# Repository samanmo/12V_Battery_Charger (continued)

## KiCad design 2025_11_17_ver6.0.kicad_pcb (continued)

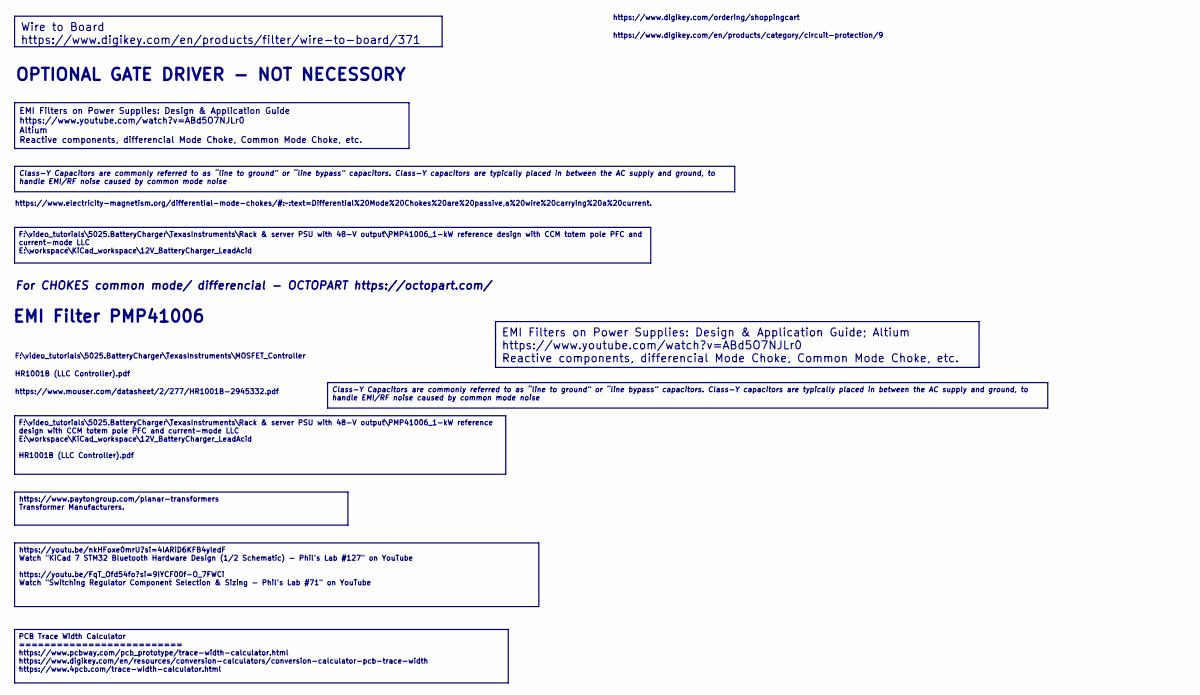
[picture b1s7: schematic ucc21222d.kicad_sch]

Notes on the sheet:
EMI Filter PMP41006
F:\video_tutorials\5025.BatteryCharger\TexasInstruments\MOSFET_Controller
https://www.digikey.com/en/products/category/circuit-protection/9
https://www.mouser.com/datasheet/2/277/HR1001B-2945332.pdf
For CHOKES common mode/ differencial - OCTOPART https://octopart.com/
https://www.digikey.com/ordering/shoppingcart
HR1001B (LLC Controller).pdf
OPTIONAL GATE DRIVER - NOT NECESSORY
https://www.electricity-magnetism.org/differential-mode-chokes/#:~:text=Differential%20Mode%20Chokes%20are%20passive,a%20wire%20carrying%20a%20current.
Wire to Board https://www.digikey.com/en/products/filter/wire-to-board/371
EMI Filters on Power Supplies: Design & Application Guide; Altium https://www.youtube.com/watch?v=ABd5O7NJLr0 Reactive components, differencial Mode Choke, Common Mode Choke, etc.
F:\video_tutorials\5025.BatteryCharger\TexasInstruments\Rack & server PSU with 48-V output\PMP41006_1-kW reference design with CCM totem pole PFC and current-mode LLC E:\workspace\KiCad_workspace\12V_BatteryCharger_LeadAcid HR1001B (LLC Controller).pdf
PCB Trace Width Calculator ========================== https://www.pcbway.com/pcb_prototype/trace-width-calculator.html https://www.digikey.com/en/resources/conversion-calculators/conversion-calculator-pcb-trace-width https://www.4pcb.com/trace-width-calculator.html
https://www.paytongroup.com/planar-transformers Transformer Manufacturers.
Class-Y Capacitors are commonly referred to as “line to ground” or “line bypass” capacitors. Class-Y capacitors are typically placed in between the AC supply and ground, to handle EMI/RF noise caused by common mode noise
F:\video_tutorials\5025.BatteryCharger\TexasInstruments\Rack & server PSU with 48-V output\PMP41006_1-kW reference design with CCM totem pole PFC and current-mode LLC E:\workspace\KiCad_workspace\12V_BatteryCharger_LeadAcid
https://youtu.be/nkHFoxe0mrU?si=4lARiD6KFB4yIedF Watch "KiCad 7 STM32 Bluetooth Hardware Design (1/2 Schematic) - Phil's Lab #127" on YouTube https://youtu.be/FqT_Ofd54fo?si=9IYCF00f-O_7FWCi Watch "Switching Regulator Component Selection & Sizing - Phil's Lab #71" on YouTube
EMI Filters on Power Supplies: Design & Application Guide https://www.youtube.com/watch?v=ABd5O7NJLr0 Altium Reactive components, differencial Mode Choke, Common Mode Choke, etc.

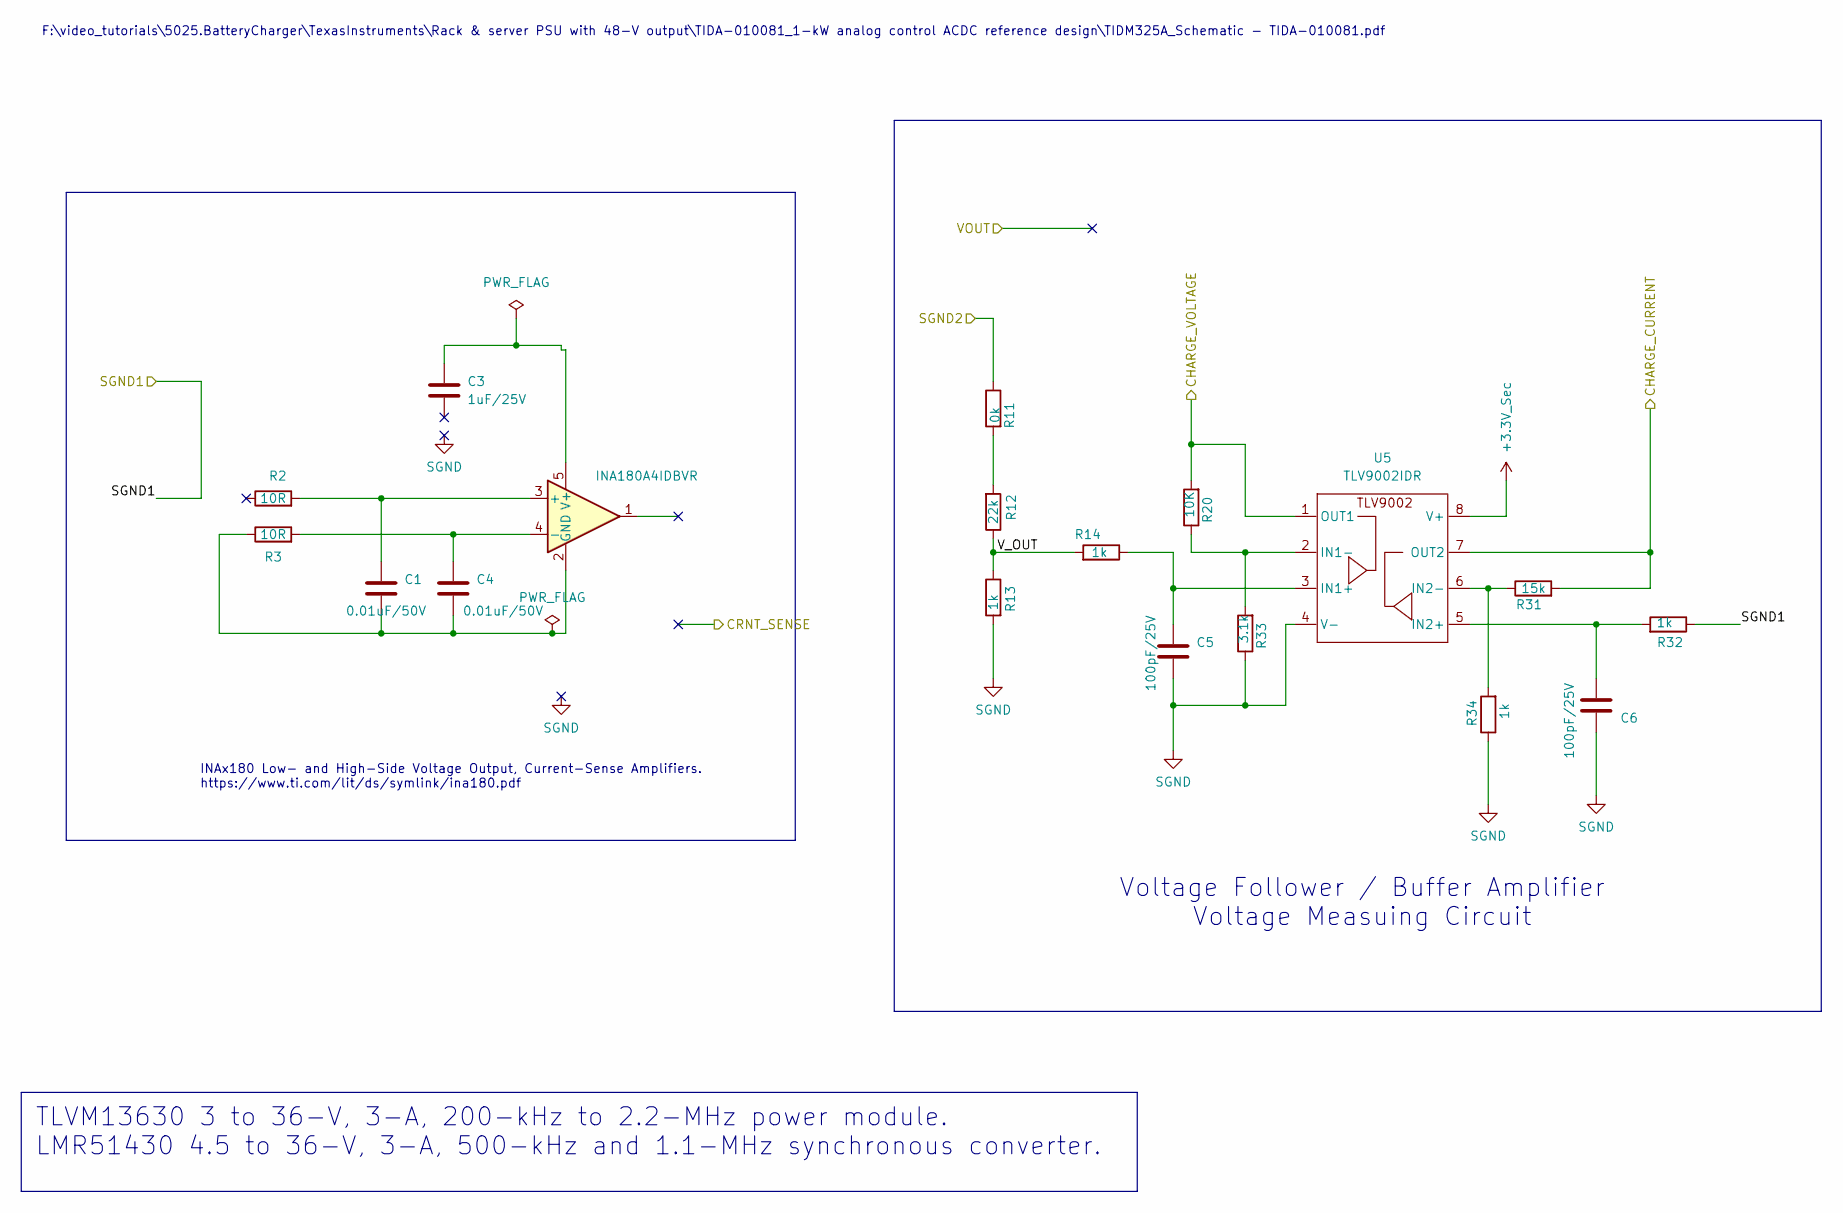
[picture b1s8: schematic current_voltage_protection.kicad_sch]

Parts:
C1, C4: 0.01uF/50V; C_0603_1608Metric_Pad1.08x0.95mm_HandSolder; Manufacturer_Part_Number GCM188R72A103KA37D; Digi-Key_PN 490-4781-1-ND
C3: 1uF/25V; C_0805_2012Metric_Pad1.18x1.45mm_HandSolder; Manufacturer_Part_Number CL21B105KBFNNNE; Digi-Key_PN 1276-1029-1-ND
C5, C6: 100pF/25V; C_0805_2012Metric_Pad1.18x1.45mm_HandSolder; Manufacturer_Part_Number CC0805KRX7R8BB103; Digi-Key_PN 311-3579-1-ND
R2, R3: 10R; R_1206_3216Metric_Pad1.30x1.75mm_HandSolder; Manufacturer_Part_Number RT1206DRE0710RL; Digi-Key_PN 311-2958-1-ND
R11: 0k; R_0805_2012Metric_Pad1.20x1.40mm_HandSolder; Manufacturer_Part_Number RC0805FR-076K8L; Digi-Key_PN 311-6.80KCRCT-ND
R12: 22k; R_0805_2012Metric_Pad1.20x1.40mm_HandSolder; Manufacturer_Part_Number RC0805FR-071KL; Digi-Key_PN 311-1.00KCRCT-ND
R13: 1k; R_0805_2012Metric_Pad1.20x1.40mm_HandSolder; Manufacturer_Part_Number RC0805FR-072K2L; Digi-Key_PN 311-2.20KCRCT-ND
R14, R32: 1k; R_0805_2012Metric_Pad1.20x1.40mm_HandSolder; Manufacturer_Part_Number RC0805FR-071KL; Digi-Key_PN 311-1.00KCRCT-ND
R20: 10K; R_0805_2012Metric_Pad1.20x1.40mm_HandSolder; Manufacturer_Part_Number RC0805JR-070RL; Digi-Key_PN 311-0.0ARCT-ND
R31: 15k; R_0805_2012Metric_Pad1.20x1.40mm_HandSolder; Manufacturer_Part_Number RC0805JR-070RL; Digi-Key_PN 311-0.0ARCT-ND
R33: 3.1k; R_0805_2012Metric_Pad1.20x1.40mm_HandSolder; Manufacturer_Part_Number RC0805JR-070RL; Digi-Key_PN 311-0.0ARCT-ND
R34: 1k; R_0805_2012Metric_Pad1.20x1.40mm_HandSolder; Manufacturer_Part_Number RC0805JR-070RL; Digi-Key_PN 311-0.0ARCT-ND
U4: INA180A4IDBVR; SOT-23-5; Manufacturer_Part_Number INA180A4IDBVR; Digi-Key_PN 296-47655-1-ND
U5: TLV9002IDR; D0008A_M; Manufacturer_Part_Number TLV9002IDR; Digi-Key_PN 296-47596-1-ND

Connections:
+3.3V_Sec: U5.8 (V+); also elsewhere on the board
/Output_Filtering/CHARGE_CURRENT_STM32: R31.2, U5.7 (OUT2); also elsewhere on the board
/Output_Filtering/CHARGE_VOLTAGE_STM32: R20.2, U5.1 (OUT1); also elsewhere on the board
/Output_Filtering/Current_voltage_protection/V_OUT: R12.1, R13.1, R14.2
/Output_Filtering/SGND1: R32.1; also elsewhere on the board
/Output_Filtering/SGND2: R11.1; also elsewhere on the board
unnamed: R11.2, R12.2
unnamed: C1.1, R2.2, U4.3 (+)
unnamed: C4.1, R3.2, U4.4 (-)
unnamed: C1.2, C4.2, R3.1, U4.2 (GND)
unnamed: C3.1, U4.5 (V+)
unnamed: C5.1, R14.1, U5.3 (IN1+)
unnamed: R20.1, R33.2, U5.2 (IN1-)
unnamed: C6.1, R32.2, U5.5 (IN2+)
unnamed: R31.1, R34.2, U5.6 (IN2-)
SGND: C5.2, C6.2, R13.2, R33.1, R34.1, U5.4 (V-); also elsewhere on the board

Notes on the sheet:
F:\video_tutorials\5025.BatteryCharger\TexasInstruments\Rack & server PSU with 48-V output\TIDA-010081_1-kW analog control ACDC reference design\TIDM325A_Schematic - TIDA-010081.pdf
INAx180 Low- and High-Side Voltage Output, Current-Sense Amplifiers. https://www.ti.com/lit/ds/symlink/ina180.pdf
Voltage Follower / Buffer Amplifier Voltage Measuing Circuit
TLVM13630 3 to 36-V, 3-A, 200-kHz to 2.2-MHz power module. LMR51430 4.5 to 36-V, 3-A, 500-kHz and 1.1-MHz synchronous converter.

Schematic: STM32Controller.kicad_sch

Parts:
C111, C115: 44uF/25V; C_1206_3216Metric_Pad1.33x1.80mm_HandSolder; Manufacturer_Part_Number C3216X5R1E476M160AC; Digi-Key_PN 445-8047-1-ND
C112, C114: 2.2uF/25V; C_0805_2012Metric_Pad1.18x1.45mm_HandSolder; Manufacturer_Part_Number CL21B225KAFNFNE; Digi-Key_PN 1276-2953-1-ND
C113: 0.1uF/25V; C_0805_2012Metric_Pad1.18x1.45mm_HandSolder; Manufacturer_Part_Number CC0805KRX7R9BB104; Digi-Key_PN 311-1140-1-ND
J4: Screw_Terminal_01x02 pwm; TerminalBlock_Phoenix_MKDS-1,5-2-5.08_1x02_P5.08mm_Horizont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
J6, J13, J14, J16: Conn_01x01_Pin; PinHeader_1x01_P2.54mm_Vertical
L12: 5.6uH/5A; L_Pulse_PA4341.562NLT_7.6x6.9mm; Manufacturer_Part_Number PA4341.562NLT; Digi-Key_PN 553-3417-1-ND
R53, R55, R56, R58, R59, R60, R62, R63: 0; R_0805_2012Metric_Pad1.20x1.40mm_HandSolder; not fitted
R150, R152: 100k; R_0805_2012Metric_Pad1.20x1.40mm_HandSolder; Manufacturer_Part_Number RC0805FR-07100KL; Digi-Key_PN 311-100KCRCT-ND
R151, R153: 22.6k; R_0805_2012Metric_Pad1.20x1.40mm_HandSolder; Manufacturer_Part_Number RC0805FR-0722K1L; Digi-Key_PN 311-22.1KCRCT-ND
R167: 0R; R_0805_2012Metric_Pad1.20x1.40mm_HandSolder; Manufacturer_Part_Number RC0805JR-070RL; Digi-Key_PN 311-0.0ARCT-ND
U6: LM317_TO-220; TO-220-3_Vertical
U10: WeAct_BluePill; WeAct_BluekPill_Correct_Size
U25: LMR51430XDDCR; SOT-23-THIN-6_DDC_TEX-M; Manufacturer_Part_Number LMR51430XDDCR; Digi-Key_PN 296-LMR51430XDDCRCT-ND

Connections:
+3.3V_Sec: J6.1, R63.1, R167.2; also elsewhere on the board
/LLC_Power/+20V: C112.1, J4.2, U25.3 (VIN), U25.5 (EN); also elsewhere on the board
/Output_Filtering/CHARGE_CURRENT_STM32: R59.1; also elsewhere on the board
/Output_Filtering/CHARGE_VOLTAGE_STM32: R56.1; also elsewhere on the board
/Output_Filtering/CRNT_SENSE_STM32: R58.1
/Output_Filtering/FBR2_STM32: R60.1; also elsewhere on the board
/Output_Filtering/FBR_STM32: R55.2; also elsewhere on the board
/Output_Filtering/STM32Controller/3V3_STM32: R63.2, U10.38 (3V3)
/Output_Filtering/STM32Controller/+3.3V_Sec_SW: C113.1, L12.2, U25.2 (SW)
/Output_Filtering/STM32Controller/+3.3V_Sec_SW1: C111.2, L12.1, R150.1, R167.1
/Output_Filtering/STM32Controller/FB_LMR51430_3V3: R150.2, R151.1, U25.4 (FB)
/Output_Filtering/STM32Controller/GND_STM32: R53.1, U10.19 (GND)
/Output_Filtering/STM32Controller/STM32_5V: R62.1
unnamed: C114.1, J13.1, U6.3 (VI)
unnamed: C115.2, J14.1, R152.1, U6.2 (VO)
unnamed: C114.2, C115.1, J16.1, R153.2
unnamed: R152.2, R153.1, U6.1 (ADJ)
unnamed: R62.2, U10.18 (5V)
unnamed: R59.2, U10.27 (PA1)
unnamed: R56.2, U10.28 (PA2)
unnamed: R58.2, U10.33 (PA7)
unnamed: R55.1, U10.5 (PA8)
unnamed: R60.2, U10.37 (PB10)
unnamed: C113.2, U25.6 (CB)
SGND: C111.1, C112.2, J4.1, R53.2, R151.2, U25.1 (GND); also elsewhere on the board

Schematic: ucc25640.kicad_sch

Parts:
C24, C30: 100pF; C_0805_2012Metric_Pad1.18x1.45mm_HandSolder
C25: 0.01uF/25V; C_0805_2012Metric_Pad1.18x1.45mm_HandSolder; Manufacturer_Part_Number CC0805KRX7R8BB103; Digi-Key_PN 311-3579-1-ND
C26, C27: 100pF/50V; C_0805_2012Metric_Pad1.18x1.45mm_HandSolder; Manufacturer_Part_Number CC0805JRNPO9BN101; Digi-Key_PN 311-1111-1-ND
C28: 2.2uF/25V; C_0805_2012Metric_Pad1.18x1.45mm_HandSolder; Manufacturer_Part_Number CL21B225KAFNFNE; Digi-Key_PN 1276-2953-1-ND
C29: 0.01uF; C_0805_2012Metric_Pad1.18x1.45mm_HandSolder
C31: 1nF/50V; C_0805_2012Metric_Pad1.18x1.45mm_HandSolder; Manufacturer_Part_Number CC0805JRNPO9BN101; Digi-Key_PN 311-1111-1-ND
C46: 2.2nF; C_0805_2012Metric_Pad1.18x1.45mm_HandSolder
C50: 4.7uF/25V; C_0805_2012Metric_Pad1.18x1.45mm_HandSolder; Manufacturer_Part_Number C2012X5R1E475K125AB; Digi-Key_PN 445-4116-1-ND
C51: 27nF/68nF/22nF/15V; C_0805_2012Metric_Pad1.18x1.45mm_HandSolder; Manufacturer_Part_Number C0805C273K5RAC7800; Digi-Key_PN 399-C0805C273K5RAC7800CT-ND
D39: 600V 1A SMA; SODFL3616X98N; Manufacturer_Part_Number SM4005PL-TP; Digi-Key_PN SM4005PL-TPMSCT-ND
D40: 100V 1A SMA; SODFL3616X98N; Manufacturer_Part_Number SM4005PL-TP; Digi-Key_PN SM4005PL-TPMSCT-ND
FB1: FerriteBead; L_0805_2012Metric_Pad1.05x1.20mm_HandSolder
IC3, IC4: UCC27517DBVR; SOT-23-5_HandSoldering; Mouser Part Number 595-UCC27517DBVR
R4, R5: 5.1M; R_0805_2012Metric_Pad1.20x1.40mm_HandSolder; Manufacturer_Part_Number RC0805FR-075M1L; Digi-Key_PN 13-RC0805FR-075M1LCT-ND
R6: 5.6M; R_0805_2012Metric_Pad1.20x1.40mm_HandSolder; Manufacturer_Part_Number RC0805FR-075M6L; Digi-Key_PN 13-RC0805FR-075M6LCT-ND
R7: 127k; R_0805_2012Metric_Pad1.20x1.40mm_HandSolder; Manufacturer_Part_Number RC0805FR-07127KL; Digi-Key_PN 311-127KCRCT-ND
R8, R9, R10, R24: 1.65K; R_0805_2012Metric_Pad1.20x1.40mm_HandSolder; Manufacturer_Part_Number RC0805FR-071K65L; Digi-Key_PN 311-1.65KCRCT-ND
R15, R17, R21: 0; R_0805_2012Metric_Pad1.20x1.40mm_HandSolder
R16: 2.00k; R_0805_2012Metric_Pad1.20x1.40mm_HandSolder
R18: 10k/8.2k; R_0805_2012Metric_Pad1.20x1.40mm_HandSolder
R19: 15k; R_0805_2012Metric_Pad1.20x1.40mm_HandSolder
R22: 30k; R_0805_2012Metric_Pad1.20x1.40mm_HandSolder
R23: 3.3k; R_0805_2012Metric_Pad1.20x1.40mm_HandSolder
R27: 100R; R_1206_3216Metric_Pad1.30x1.75mm_HandSolder; Manufacturer_Part_Number RC1206FR-07100RL; Digi-Key_PN 311-100FRCT-ND
R28: 10R; R_1206_3216Metric_Pad1.30x1.75mm_HandSolder; Manufacturer_Part_Number RC1206FR-07100RL; Digi-Key_PN 311-100FRCT-ND
R41: 2.2R; R_1206_3216Metric_Pad1.30x1.75mm_HandSolder; Manufacturer_Part_Number RC1206FR-072R2L; Digi-Key_PN 311-2.20FRCT-ND
R42: 549k; R_0805_2012Metric_Pad1.20x1.40mm_HandSolder; Manufacturer_Part_Number RC0805FR-07549KL; Digi-Key_PN 311-549KCRCT-ND
R43: 195k; R_0805_2012Metric_Pad1.20x1.40mm_HandSolder; Manufacturer_Part_Number RC0805FR-07140KL; Digi-Key_PN 311-140KCRCT-ND
R44, R45: 0R; R_0805_2012Metric_Pad1.20x1.40mm_HandSolder; Manufacturer_Part_Number RC0805JR-070RL; Digi-Key_PN 311-0.0ARCT-ND
R46, R47, R68: 0; R_0805_2012Metric_Pad1.20x1.40mm_HandSolder; Manufacturer_Part_Number RC0805FR-07549KL; Digi-Key_PN 311-549KCRCT-ND
R57: 1k; R_0805_2012Metric_Pad1.20x1.40mm_HandSolder
R69, R70: 8R; R_0805_2012Metric_Pad1.20x1.40mm_HandSolder
U1: VO618A; SMD-4-OPT7_VO618A_VIS-M
U2: UCC256404DDBR; DDB0014A-IPC_A
U3: TL431LP; TO-92_Inline_Wide

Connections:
/LLC_Power/BW: U2.8 (BW); also elsewhere on the board
/LLC_Power/ISNS: U2.6 (ISNS); also elsewhere on the board
/LLC_Power/LLC-HOA: R44.2; also elsewhere on the board
/LLC_Power/LLC-HSA: C28.2, IC3.2 (GND), IC3.4 (IN-), U2.16 (HS); also elsewhere on the board
/LLC_Power/LLC-LOA: R45.2; also elsewhere on the board
/LLC_Power/RVCC: C50.1, IC4.1 (VDD), R41.2, R46.1, U2.12 (RVCC)
/LLC_Power/UCC25640/BLK: C25.1, R6.2, R7.1, R27.1
/LLC_Power/UCC25640/BLK1: C26.1, R27.2, U2.4 (BLK)
/LLC_Power/UCC25640/FB: FB1.1, R28.1
/LLC_Power/UCC25640/FB1: C27.1, R28.2, U2.5 (FB)
/LLC_Power/UCC25640/HB: C28.1, D40.1 (K), IC3.1 (VDD), U2.14 (HB)
/LLC_Power/UCC25640/LL: C51.2, R42.2, R47.1, U2.9 (LL_SS)
/LLC_Power/UCC25640/VCCP1: R68.2, U2.3 (VCC)
/LLC_Power/VCCP: R68.1; also elsewhere on the board
/LLC_Power/VCR: U2.7 (VCR); also elsewhere on the board
/LLC_Power/V_BUS: R4.1, R10.1; also elsewhere on the board
/VOUT: R15.1; also elsewhere on the board
unnamed: C24.1, FB1.2, U1.4
unnamed: C29.2, R22.1
unnamed: C46.1, R57.2
unnamed: C46.2, R15.2, R17.2, R18.2
unnamed: D39.2 (A), R41.1
unnamed: D39.1 (K), D40.2 (A)
unnamed: IC3.3 (IN+), R69.2
unnamed: IC3.5 (OUT), R44.1
unnamed: IC4.3 (IN+), R70.2
unnamed: IC4.5 (OUT), R45.1
unnamed: R4.2, R5.1
unnamed: R5.2, R6.1
unnamed: R8.2, R9.1
unnamed: R8.1, R10.2
unnamed: R16.1, R18.1, R57.1, U1.1
unnamed: R17.1, R19.1
unnamed: R21.1, U1.3
unnamed: R9.2, R24.1
unnamed: R42.1, R46.2
unnamed: R43.1, R47.2
unnamed: R69.1, U2.15 (HO)
unnamed: R24.2, U2.1 (HV)
unnamed: R70.1, U2.10 (LO)
unnamed: C29.1, C30.1, R16.2, U1.2, U3.3 (K)
unnamed: C30.2, C31.1, R19.2, R22.2, R23.1, U3.1 (REF)
PGND1: C24.2, C25.2, C26.2, C27.2, C50.2, C51.1, IC4.2 (GND), IC4.4 (IN-), R7.2, R21.2, R43.2, U2.11 (GND); also elsewhere on the board
SGND: C31.2, R23.2, U3.2 (A); also elsewhere on the board

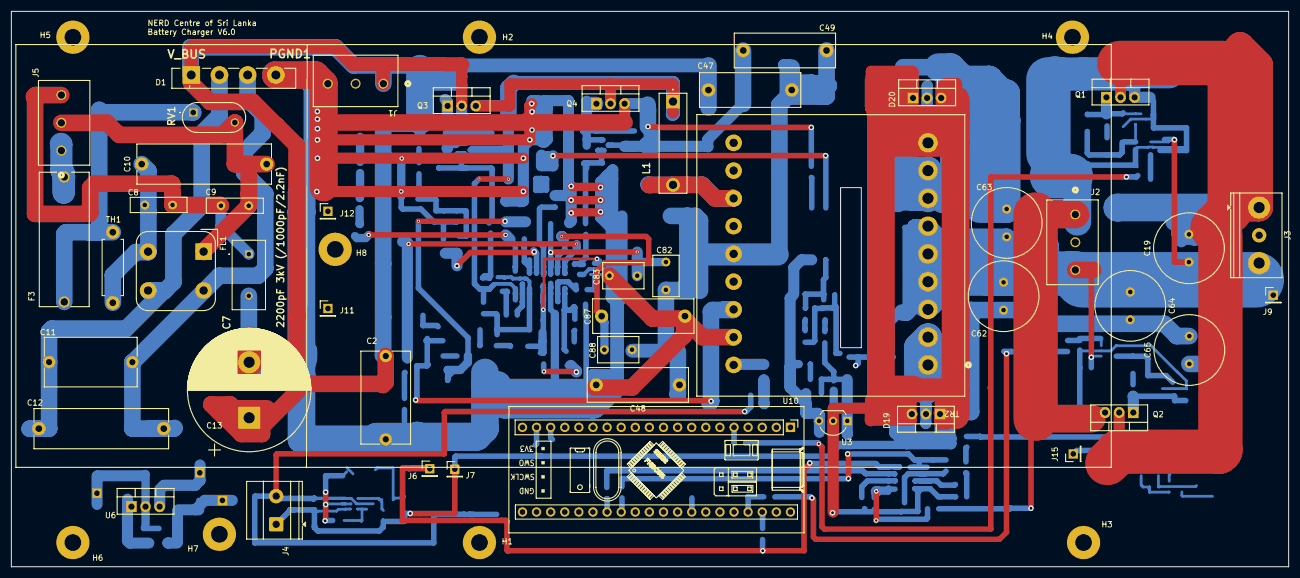
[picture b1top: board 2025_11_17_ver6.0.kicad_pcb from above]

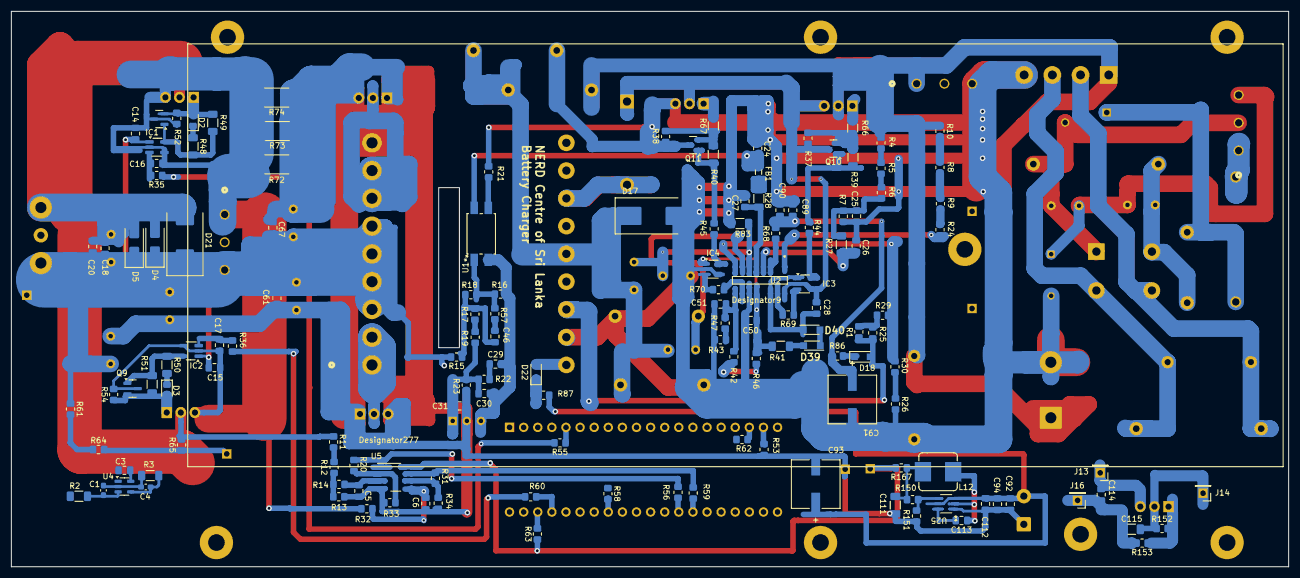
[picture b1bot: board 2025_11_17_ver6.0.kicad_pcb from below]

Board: 2 copper layers, 230.0 x 100.0 mm, 199 parts (144 on the bottom side), 109 nets.
